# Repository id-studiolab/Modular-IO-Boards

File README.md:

# Modular-IO-Boards

### :warning: **Repository Not Maintained** :warning:
### Please visit [EduGroveModules - CustomComponents](https://github.com/id-studiolab/EduGroveModules/tree/main/CustomComponents) for up-to-date information on this project.

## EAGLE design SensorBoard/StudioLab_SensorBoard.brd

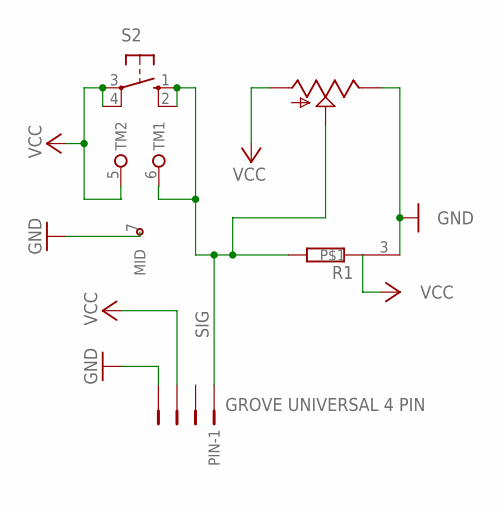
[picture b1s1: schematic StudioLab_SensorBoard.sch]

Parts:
PIN: GROVE UNIVERSAL 4 PIN; CON-JST_B4B-ZR
R1: RES_PULL_UP_DOWNRES_PULL_UP_DOWN_ANGLE; RES_PULL_UP_DOWN_ANGLE
S2: TERMINAL_TAC_SWITCH; TERMINAL_TACTILE-PTH
U$1: SPARKFUN_POT; SPARKFUN_ALPS_POT

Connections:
GND: PIN.4, R1.3, S2.7 (MID), U$1.P$1 (E)
SIG: PIN.1, R1.1 (2), S2.1 (3), S2.2 (4), S2.6 (TM1), U$1.P$2 (S)
VCC: PIN.3, R1.2 (1), S2.3 (1), S2.4 (2), S2.5 (TM2), U$1.P$3 (A)

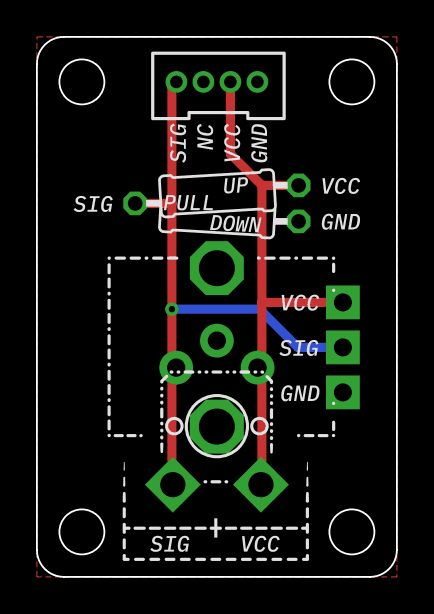
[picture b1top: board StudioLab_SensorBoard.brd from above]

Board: 2 copper layers, 20.0 x 30.0 mm, 4 parts (0 on the bottom side), 3 nets.

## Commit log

2020-06-24 Schematics and renderings
    Initial commit, schematics and demo renderings
